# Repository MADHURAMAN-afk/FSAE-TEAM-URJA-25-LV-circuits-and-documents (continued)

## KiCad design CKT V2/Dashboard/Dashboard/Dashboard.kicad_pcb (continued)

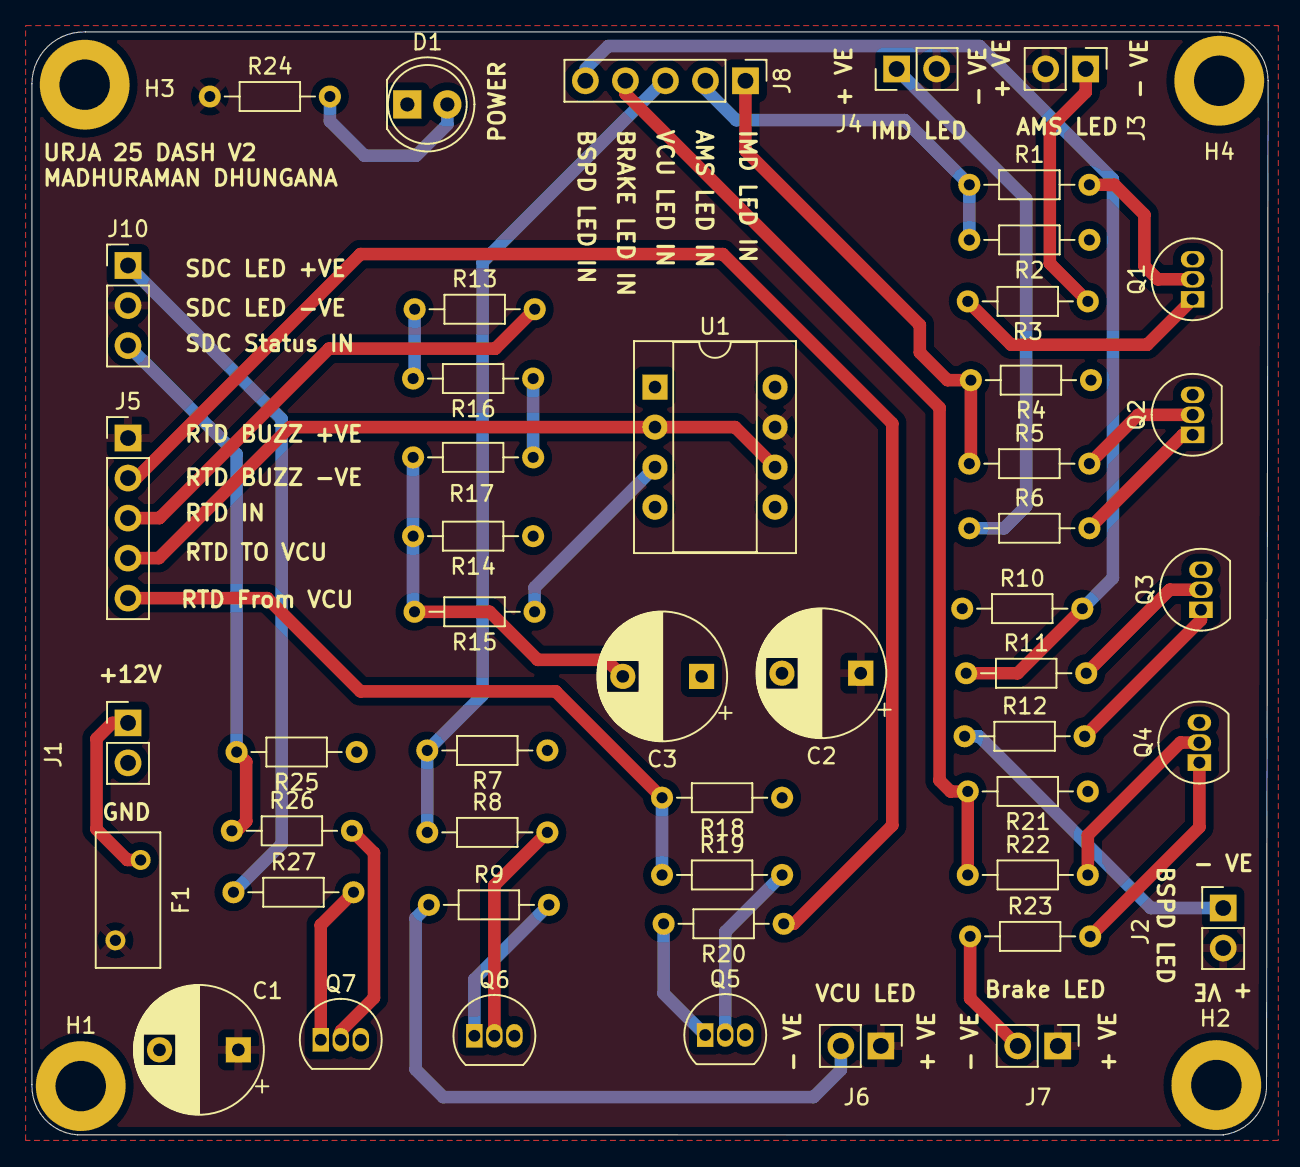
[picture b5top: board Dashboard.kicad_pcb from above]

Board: 2 copper layers, 78.5 x 70.0 mm, 53 parts (0 on the bottom side), 38 nets.

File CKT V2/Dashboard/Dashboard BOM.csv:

"Reference","Value","Qty"
"C1,C2,C3","0.1","3"
"D1","LED","1"
"F1","Polyfuse","1"
"J1,J2,J3,J4,J6,J7","Conn_01x02_Pin","6"
"J5,J8","Conn_01x05_Pin","2"
"J10","Conn_01x03_Pin","1"
"Q1,Q2,Q3,Q4,Q5,Q6,Q7","BC547","7"
"R1,R5,R8,R11,R19,R22,R26","100","7"
"R2,R4,R7,R10,R15,R18,R21,R25","10k","8"
"R3,R6,R9,R12,R20,R23,R27","220","7"
"R13","390","1"
"R14","1k","1"
"R16","2.2k","1"
"R17","10","1"
"R24","1K","1"
"U1","LM741","1"

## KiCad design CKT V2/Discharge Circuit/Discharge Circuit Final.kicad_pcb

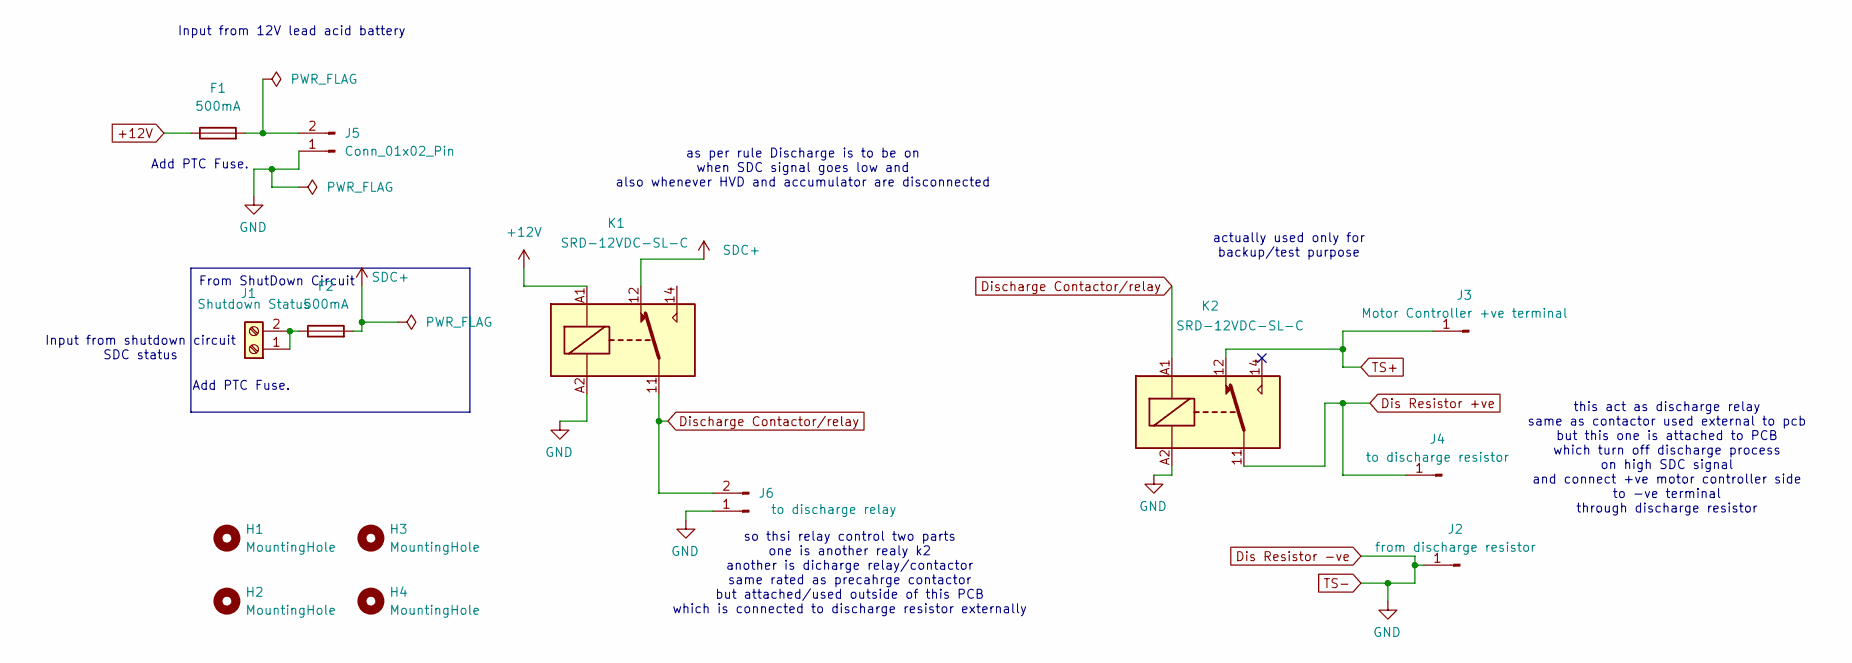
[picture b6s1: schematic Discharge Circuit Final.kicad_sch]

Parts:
F1, F2: 500mA; Fuse_BelFuse_0ZRE0008FF_L8.3mm_W3.8mm
H1, H2, H3, H4: MountingHole; MountingHole_4.3mm_M4
J1: Shutdown Status; TerminalBlock_Phoenix_MKDS-1,5-2-5.08_1x02_P5.08mm_Horizont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
J2: from discharge resistor; TerminalBlock_Phoenix_MKDS-1,5-2-5.08_1x02_P5.08mm_Horizont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
J3: Motor Controller +ve terminal; TerminalBlock_Phoenix_MKDS-1,5-2-5.08_1x02_P5.08mm_Horizont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
J4: to discharge resistor; TerminalBlock_Phoenix_MKDS-1,5-2-5.08_1x02_P5.08mm_Horizont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
J5: Conn_01x02_Pin; TerminalBlock_Phoenix_MKDS-1,5-2-5.08_1x02_P5.08mm_Horizont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
J6: to discharge relay; TerminalBlock_Phoenix_MKDS-1,5-2-5.08_1x02_P5.08mm_Horizont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
K1, K2: SRD-12VDC-SL-C; Relay_SPDT_Hongfa_HF3F-L-xx-1ZL1T

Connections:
+12V: F1.1, K1.A1
Dis Resistor +ve: J4.1, K2.11
Dis Resistor -ve: J2.1, J5.1, J6.1, K1.A2, K2.A2
Discharge Contactor/relay: J6.2, K1.11, K2.A1
unnamed: F2.1, J1.1, J1.2
unnamed: F1.2, J5.2
SDC+: F2.2, K1.12
TS+: J3.1, K2.12

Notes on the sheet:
From ShutDown Circuit
Add PTC Fuse.
as per rule Discharge is to be on when SDC signal goes low and also whenever HVD and accumulator are disconnected
actually used only for backup/test purpose
so thsi relay control two parts one is another realy k2 another is dicharge relay/contactor same rated as precahrge contactor but attached/used outside of this PCB which is connected to discharge resistor externally
Input from 12V lead acid battery
Input from shutdown circuit SDC status
this act as discharge relay same as contactor used external to pcb but this one is attached to PCB which turn off discharge process on high SDC signal and connect +ve motor controller side to -ve terminal through discharge resistor

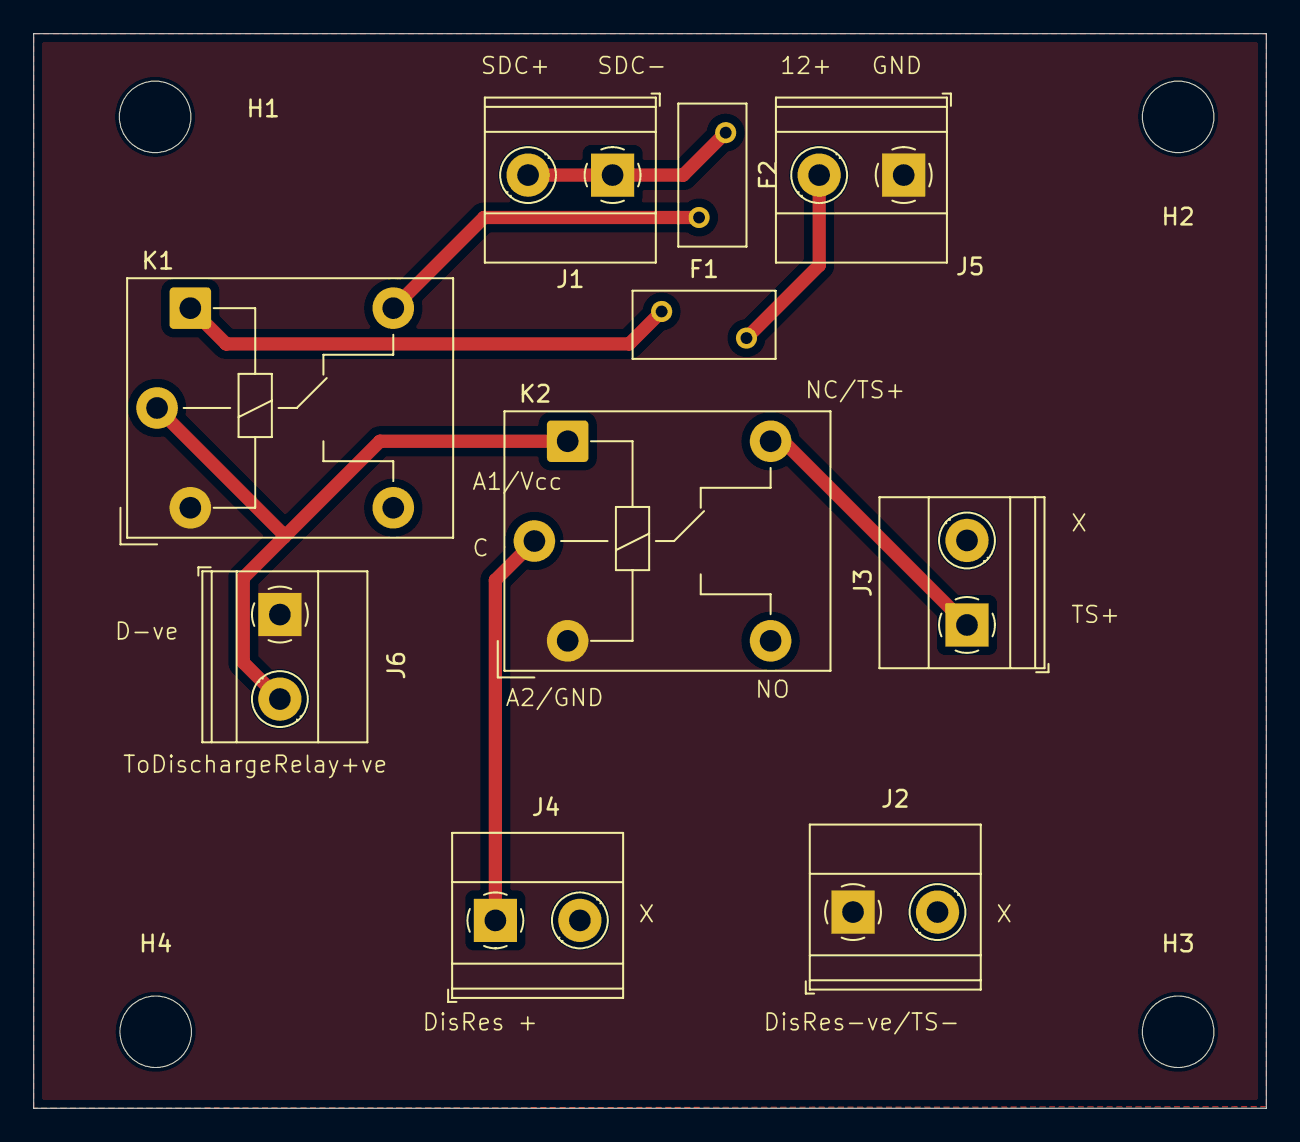
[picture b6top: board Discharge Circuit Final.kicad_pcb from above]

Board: 2 copper layers, 74.1 x 64.6 mm, 14 parts (0 on the bottom side), 8 nets.

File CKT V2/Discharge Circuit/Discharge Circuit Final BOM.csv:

Reference,Value,Footprint,Qty,DNP
"F1,F2",500mA,Fuse:Fuse_BelFuse_0ZRE0008FF_L8.3mm_W3.8mm,2,
J1,Shutdown Status,"TerminalBlock_Phoenix:TerminalBlock_Phoenix_MKDS-1,5-2-5.08_1x02_P5.08mm_Horizontal",1,
J2,from discharge resistor,"TerminalBlock_Phoenix:TerminalBlock_Phoenix_MKDS-1,5-2-5.08_1x02_P5.08mm_Horizontal",1,
J3,Motor Controller +ve terminal,"TerminalBlock_Phoenix:TerminalBlock_Phoenix_MKDS-1,5-2-5.08_1x02_P5.08mm_Horizontal",1,
J4,to discharge resistor,"TerminalBlock_Phoenix:TerminalBlock_Phoenix_MKDS-1,5-2-5.08_1x02_P5.08mm_Horizontal",1,
J5,Conn_01x02_Pin,"TerminalBlock_Phoenix:TerminalBlock_Phoenix_MKDS-1,5-2-5.08_1x02_P5.08mm_Horizontal",1,
J6,to discharge relay,"TerminalBlock_Phoenix:TerminalBlock_Phoenix_MKDS-1,5-2-5.08_1x02_P5.08mm_Horizontal",1,
"K1,K2",SRD-12VDC-SL-C,Relay_THT:Relay_SPDT_Hongfa_HF3F-L-xx-1ZL1T,2,

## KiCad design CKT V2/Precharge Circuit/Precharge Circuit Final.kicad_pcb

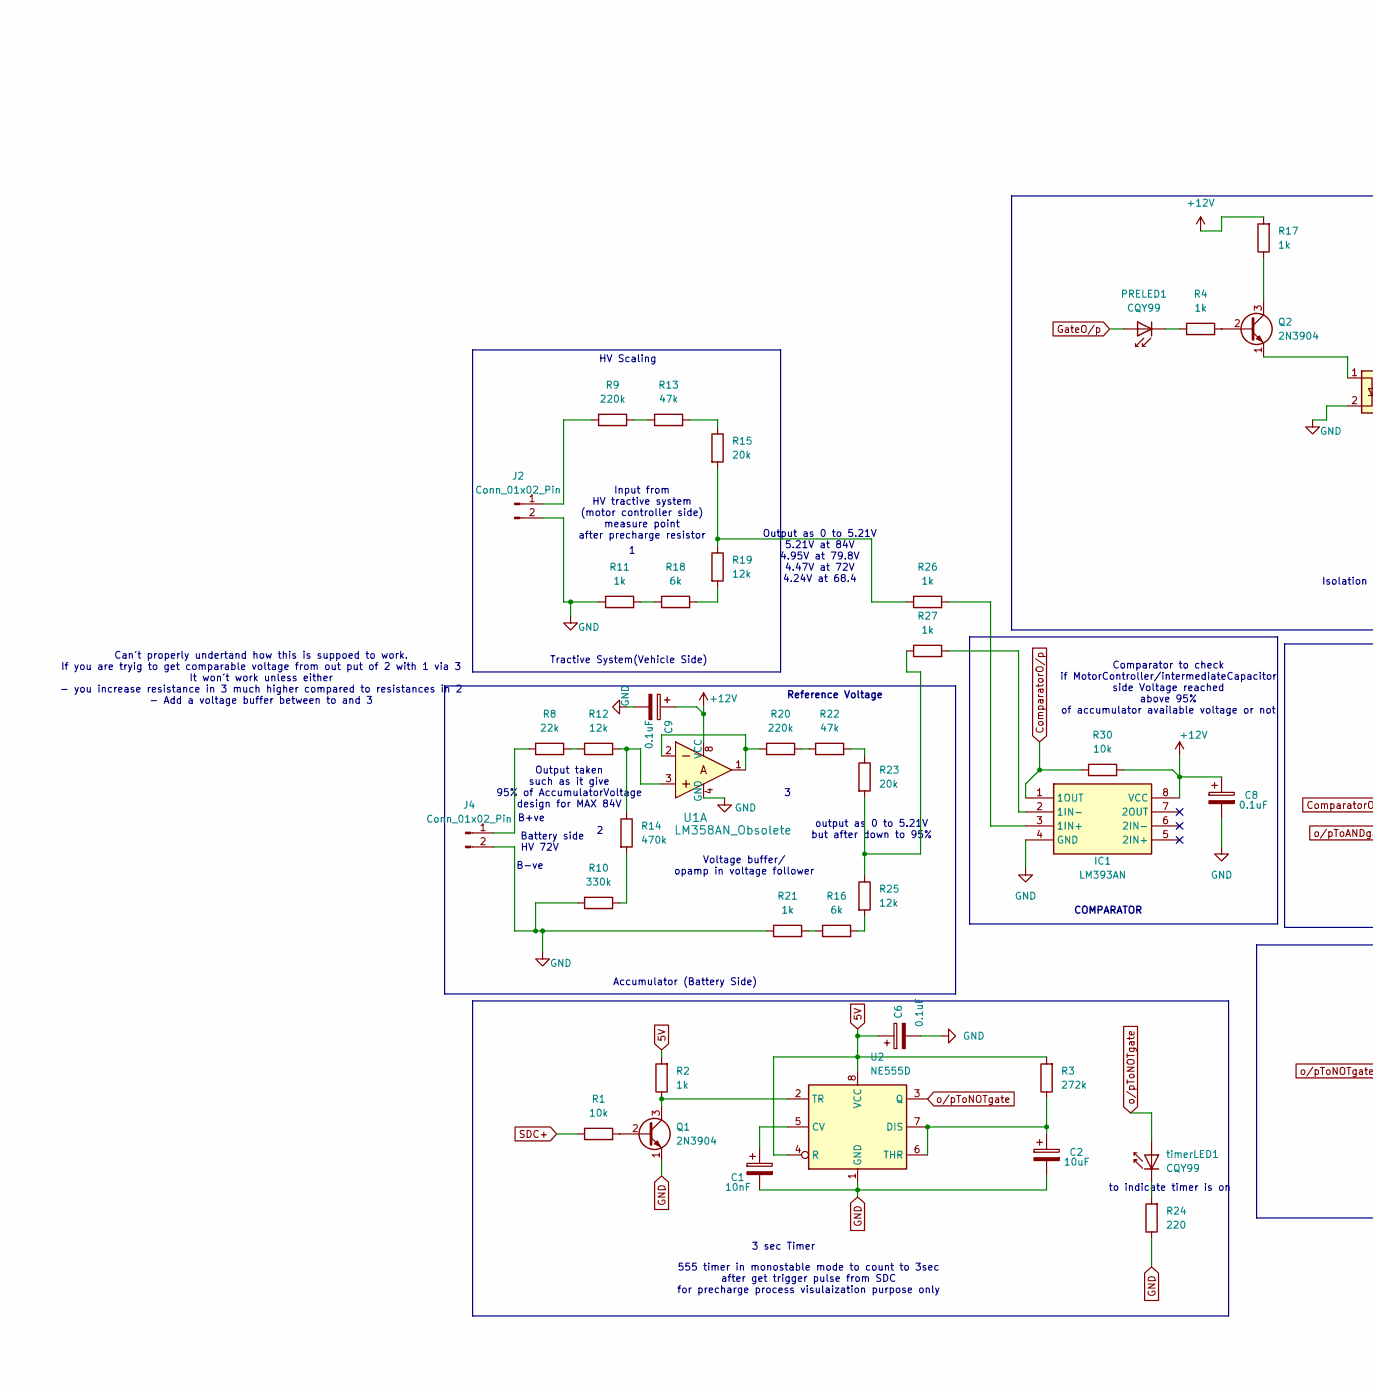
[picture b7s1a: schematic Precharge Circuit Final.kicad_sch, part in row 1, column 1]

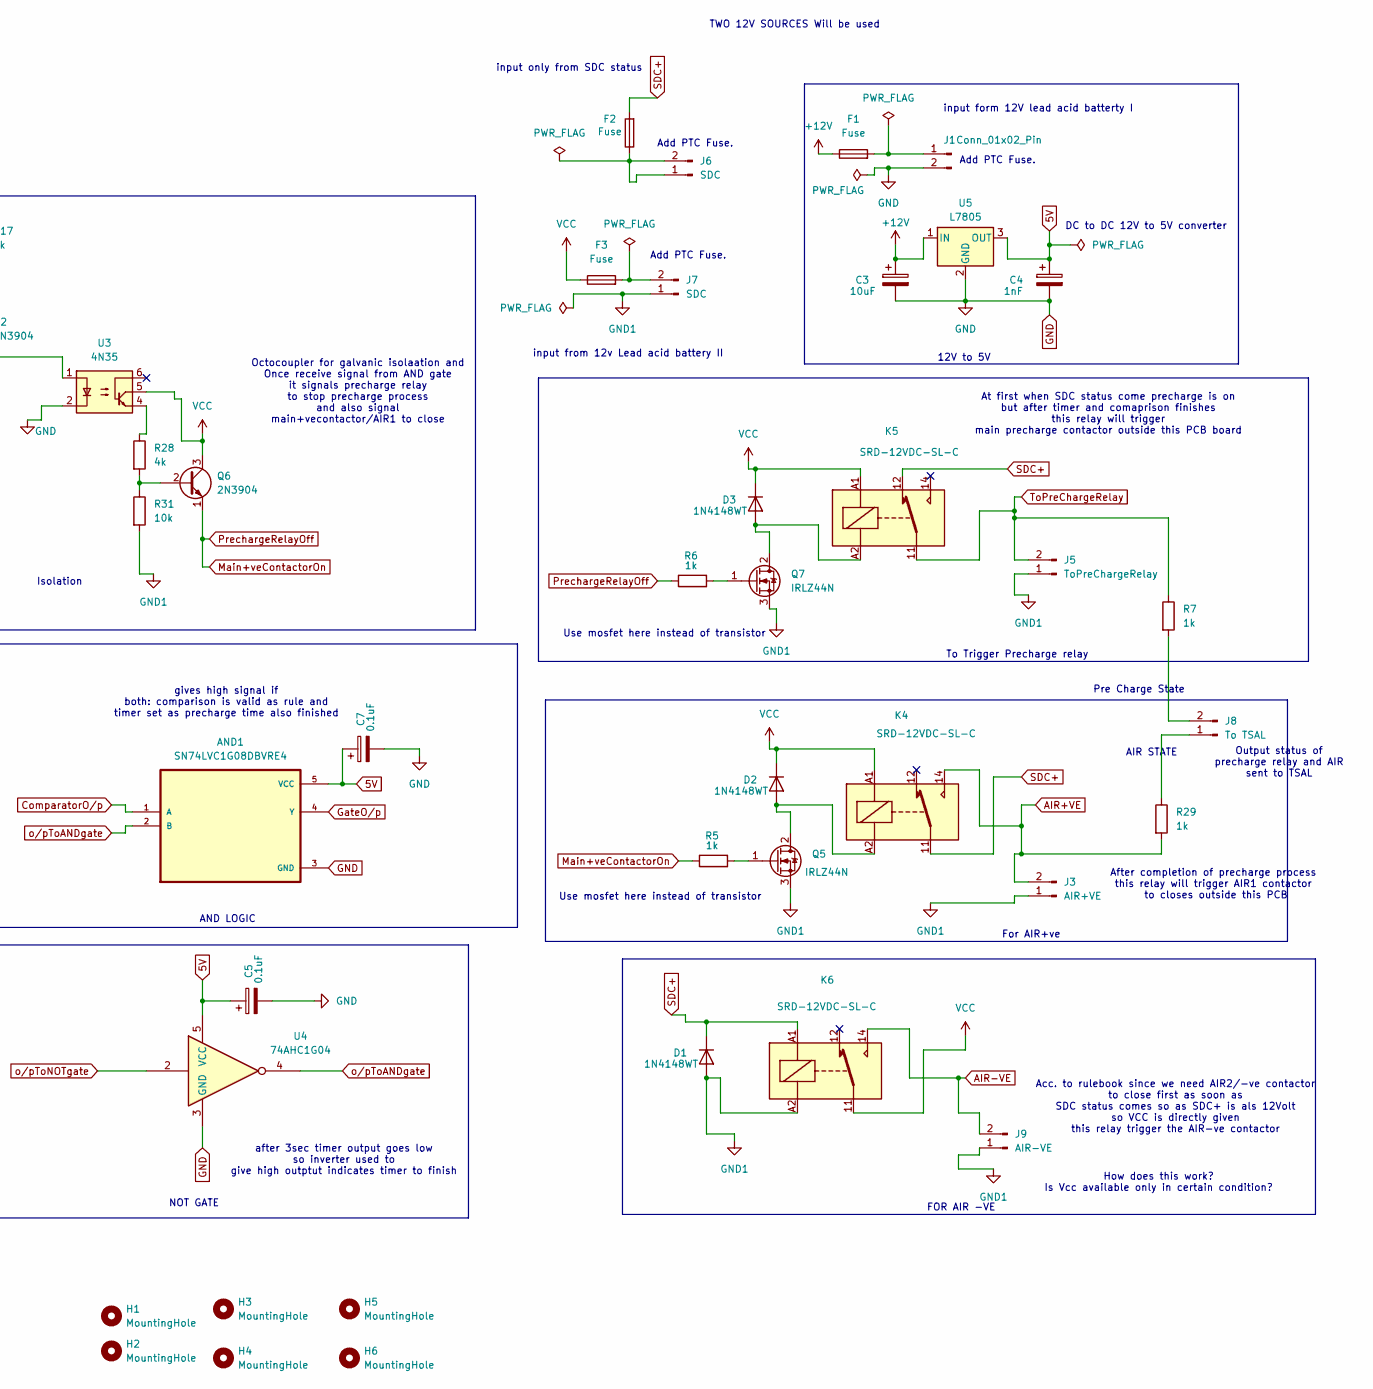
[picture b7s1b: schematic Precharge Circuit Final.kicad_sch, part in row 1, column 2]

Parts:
AND1: SN74LVC1G08DBVRE4; SOT95P280X145-5N
C1: 10nF; CP_Radial_D4.0mm_P2.00mm
C2, C3: 10uF; CP_Radial_D4.0mm_P2.00mm
C4: 1nF; CP_Radial_D4.0mm_P2.00mm
C5, C6, C7, C8, C9: 0.1uF; CP_Radial_D4.0mm_P2.00mm
D1, D2, D3: 1N4148WT; D_A-405_P7.62mm_Horizontal
F1, F2, F3: Fuse; Fuse_BelFuse_0ZRE0005FF_L8.3mm_W3.8mm
H1, H2, H3, H4, H5, H6: MountingHole; MountingHole_4.3mm_M4
IC1: LM393AN; DIP-8_W7.62mm_Socket; Manufacturer_Part_Number LM393AN; Mouser Part Number N/A
J1, J2, J4: Conn_01x02_Pin; TerminalBlock_Phoenix_MKDS-1,5-2-5.08_1x02_P5.08mm_Horizont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
J3: AIR+VE; TerminalBlock_Phoenix_MKDS-1,5-2-5.08_1x02_P5.08mm_Horizont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
J5: ToPreChargeRelay; TerminalBlock_Phoenix_MKDS-1,5-2-5.08_1x02_P5.08mm_Horizont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
J6, J7: SDC; TerminalBlock_Phoenix_MKDS-1,5-2-5.08_1x02_P5.08mm_Horizont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
J8: To TSAL; TerminalBlock_Phoenix_MKDS-1,5-2-5.08_1x02_P5.08mm_Horizont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
J9: AIR-VE; TerminalBlock_Phoenix_MKDS-1,5-2-5.08_1x02_P5.08mm_Horizont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
K4, K5, K6: SRD-12VDC-SL-C; Relay_SPDT_Hongfa_HF3F-L-xx-1ZL1T
PRELED1: CQY99; LED_D5.0mm_IRGrey
Q1, Q2, Q6: 2N3904; TO-92_Inline_Wide
Q5, Q7: IRLZ44N; TO-220-3_Vertical
R1, R30, R31: 10k; R_Axial_DIN0207_L6.3mm_D2.5mm_P10.16mm_Horizontal
R2, R4, R5, R6, R7, R11, R17, R21, R26, R27, R29: 1k; R_Axial_DIN0207_L6.3mm_D2.5mm_P10.16mm_Horizontal
R3: 272k; R_Axial_DIN0207_L6.3mm_D2.5mm_P10.16mm_Horizontal
R8: 22k; R_Axial_DIN0207_L6.3mm_D2.5mm_P10.16mm_Horizontal
R9, R20: 220k; R_Axial_DIN0207_L6.3mm_D2.5mm_P10.16mm_Horizontal
R10: 330k; R_Axial_DIN0207_L6.3mm_D2.5mm_P10.16mm_Horizontal
R12, R19, R25: 12k; R_Axial_DIN0207_L6.3mm_D2.5mm_P10.16mm_Horizontal
R13, R22: 47k; R_Axial_DIN0207_L6.3mm_D2.5mm_P10.16mm_Horizontal
R14: 470k; R_Axial_DIN0207_L6.3mm_D2.5mm_P10.16mm_Horizontal
R15, R23: 20k; R_Axial_DIN0207_L6.3mm_D2.5mm_P10.16mm_Horizontal
R16, R18: 6k; R_Axial_DIN0207_L6.3mm_D2.5mm_P10.16mm_Horizontal
R24: 220; R_Axial_DIN0207_L6.3mm_D2.5mm_P10.16mm_Horizontal
R28: 4k; R_Axial_DIN0207_L6.3mm_D2.5mm_P10.16mm_Horizontal
U1: LM358AN_Obsolete; DIP-8_W7.62mm; MPN LM358AN; Digi-Key_PN LM358ANFS-ND
U2: NE555D; DIP-8_W7.62mm
U3: 4N35; DIP-6_W7.62mm
U4: 74AHC1G04; SOT-23-5
U5: L7805; TO-220-3_Vertical
timerLED1: CQY99; LED_D5.0mm_IRGrey

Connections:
5V: AND1.5 (VCC), C4.1, C5.1, C6.1, C7.1, R2.2, R3.2, U2.4 (R), U2.8 (VCC), U4.5 (VCC), U5.3 (OUT)
+12V: C3.1, C8.1, C9.1, F1.1, IC1.8 (VCC), R17.2, R30.2, U1.8 (VCC), U5.1 (IN)
AIR+VE: J3.2, K4.14, R29.2
AIR-VE: J9.2, K6.14
ComparatorO/p: AND1.1 (A), IC1.1 (1OUT), R30.1
GND: AND1.3 (GND), C1.2, C2.2, C3.2, C4.2, C5.2, C6.2, C7.2, C8.2, C9.2, IC1.4 (GND), J1.2, J2.2, J4.2, Q1.1 (E), R10.2, R11.1, R21.1, R24.1, U1.4 (GND), U2.1 (GND), U3.2, U4.3 (GND), U5.2 (GND)
GND1: D1.2 (A), J3.1, J5.1, J7.1, J9.1, K6.A2, Q5.3 (S), Q7.3 (S), R31.2
GateO/p: AND1.4 (Y), PRELED1.2 (A)
Main+veContactorOn: Q6.1 (E), R5.1, R6.1
unnamed: D2.2 (A), K4.A2, Q5.2 (D)
unnamed: D3.2 (A), K5.A2, Q7.2 (D)
unnamed: IC1.3 (1IN+), R26.2
unnamed: IC1.2 (1IN-), R27.2
unnamed: F1.2, J1.1
unnamed: J2.1, R9.2
unnamed: J4.1, R8.2
unnamed: F2.1, J6.1, J6.2
unnamed: F3.2, J7.2
unnamed: J8.1, R29.1
unnamed: J8.2, R7.2
unnamed: PRELED1.1 (K), R4.1
unnamed: Q1.2 (B), R1.2
unnamed: Q1.3 (C), R2.1, U2.2 (TR)
unnamed: Q2.2 (B), R4.2
unnamed: Q2.3 (C), R17.1
unnamed: Q2.1 (E), U3.1
unnamed: Q5.1 (G), R5.2
unnamed: Q6.2 (B), R28.2, R31.1
unnamed: Q7.1 (G), R6.2
unnamed: R10.1, R14.2
unnamed: R11.2, R18.1
unnamed: R8.1, R12.1
unnamed: R12.2, R14.1, U1.3
unnamed: R9.1, R13.1
unnamed: R13.2, R15.1
unnamed: R15.2, R19.1, R26.1
unnamed: R16.1, R21.2
unnamed: R16.2, R25.2
unnamed: R18.2, R19.2
unnamed: R20.1, R22.1
unnamed: R20.2, U1.1, U1.2
unnamed: R22.2, R23.1
unnamed: R23.2, R25.1, R27.1
unnamed: R28.1, U3.4
unnamed: C1.1, U2.5 (CV)
unnamed: C2.1, R3.1, U2.6 (THR), U2.7 (DIS)
unnamed: R24.2, timerLED1.1 (K)
SDC+: D1.1 (K), F2.2, K4.11, K5.12, K6.A1, R1.1
ToPreChargeRelay: J5.2, K5.11, R7.1
VCC: D2.1 (K), D3.1 (K), F3.1, K4.A1, K5.A1, K6.11, Q6.3 (C), U3.5
o/pToANDgate: AND1.2 (B), U4.4
o/pToNOTgate: U2.3 (Q), U4.2, timerLED1.2 (A)

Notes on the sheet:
Acc. to rulebook since we need AIR2/-ve contactor to close first as soon as SDC status comes so as SDC+ is als 12Volt so VCC is directly given this relay trigger the AIR-ve contactor
B+ve
FOR AIR -VE
After completion of precharge process this relay will trigger AIR1 contactor to closes outside this PCB
TWO 12V SOURCES Will be used
Output taken such as it give 95% of AccumulatorVoltage design for MAX 84V
B-ve
Battery side
output as 0 to 5.21V but after down to 95%
Add PTC Fuse.
COMPARATOR
Output status of precharge relay and AIR sent to TSAL
input only from SDC status
NOT GATE
Comparator to check if MotorController/intermediateCapacitor side Voltage reached above 95% of accumulator available voltage or not
Isolation
How does this work? Is Vcc available only in certain condition?
At first when SDC status come precharge is on but after timer and comaprison finishes this relay will trigger main precharge contactor outside this PCB board
Use mosfet here instead of transistor
3 sec Timer
after 3sec timer output goes low so inverter used to give high outptut indicates timer to finish
Reference Voltage
Pre Charge State
12V to 5V
555 timer in monostable mode to count to 3sec after get trigger pulse from SDC for precharge process visulaization purpose only
gives high signal if both: comparison is valid as rule and timer set as precharge time also finished
input form 12V lead acid batterty I
Output as 0 to 5.21V 5.21V at 84V 4.95V at 79.8V 4.47V at 72V 4.24V at 68.4
AIR STATE
DC to DC 12V to 5V converter
Tractive System(Vehicle Side)
HV 72V
Octocoupler for galvanic isolaation and Once receive signal from AND gate it signals precharge relay to stop precharge process and also signal main+vecontactor/AIR1 to close
Voltage buffer/ opamp in voltage follower
HV Scaling
Input from HV tractive system (motor controller side) measure point after precharge resistor
For AIR+ve
AND LOGIC
to indicate timer is on
Accumulator (Battery Side)

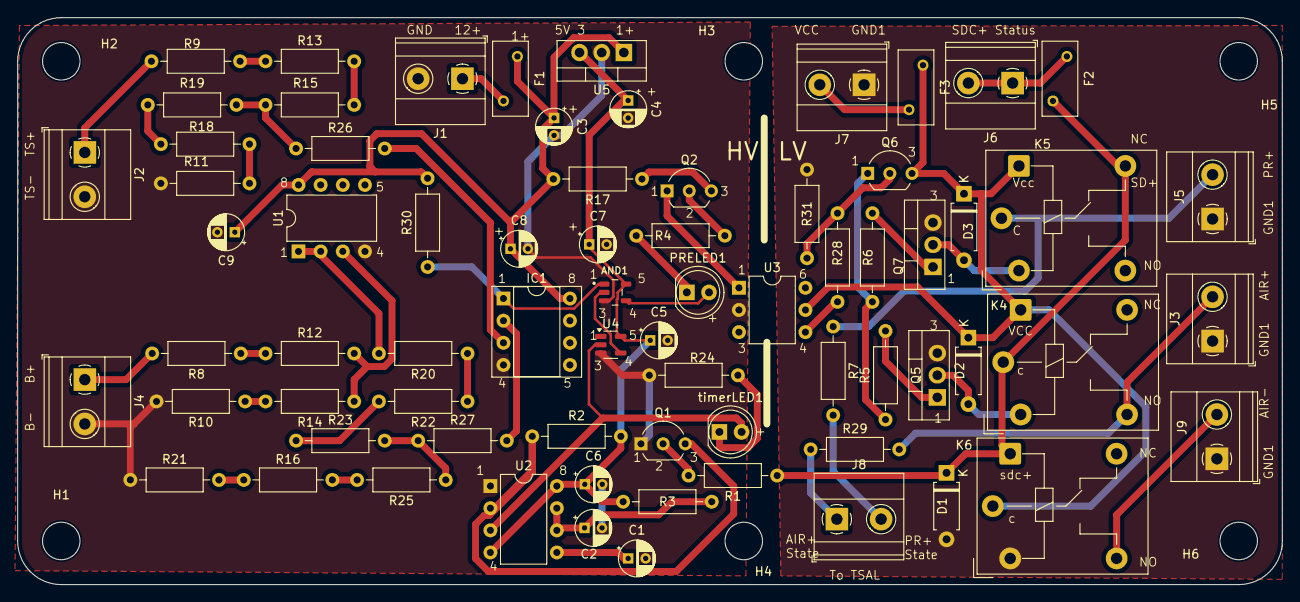
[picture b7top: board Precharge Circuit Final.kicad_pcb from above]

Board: 2 copper layers, 145.0 x 65.0 mm, 78 parts (0 on the bottom side), 52 nets.

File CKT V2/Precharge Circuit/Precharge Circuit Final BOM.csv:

Reference,Value,Footprint,Qty,DNP
AND1,SN74LVC1G08DBVRE4,SN74LVC1G08DBVRE4:SOT95P280X145-5N,1,
C1,10nF,Capacitor_THT:CP_Radial_D4.0mm_P2.00mm,1,
"C2,C3",10uF,Capacitor_THT:CP_Radial_D4.0mm_P2.00mm,2,
C4,1nF,Capacitor_THT:CP_Radial_D4.0mm_P2.00mm,1,
"C5,C6,C7,C8,C9",0.1uF,Capacitor_THT:CP_Radial_D4.0mm_P2.00mm,5,
"D1,D2,D3",1N4148WT,Diode_THT:D_A-405_P7.62mm_Horizontal,3,
"F1,F2,F3",Fuse,Fuse:Fuse_BelFuse_0ZRE0005FF_L8.3mm_W3.8mm,3,
IC1,LM393AN,Package_DIP:DIP-8_W7.62mm_Socket,1,
"J1,J2,J4",Conn_01x02_Pin,"TerminalBlock_Phoenix:TerminalBlock_Phoenix_MKDS-1,5-2-5.08_1x02_P5.08mm_Horizontal",3,
J3,AIR+VE,"TerminalBlock_Phoenix:TerminalBlock_Phoenix_MKDS-1,5-2-5.08_1x02_P5.08mm_Horizontal",1,
J5,ToPreChargeRelay,"TerminalBlock_Phoenix:TerminalBlock_Phoenix_MKDS-1,5-2-5.08_1x02_P5.08mm_Horizontal",1,
"J6,J7",SDC,"TerminalBlock_Phoenix:TerminalBlock_Phoenix_MKDS-1,5-2-5.08_1x02_P5.08mm_Horizontal",2,
J8,To TSAL,"TerminalBlock_Phoenix:TerminalBlock_Phoenix_MKDS-1,5-2-5.08_1x02_P5.08mm_Horizontal",1,
J9,AIR-VE,"TerminalBlock_Phoenix:TerminalBlock_Phoenix_MKDS-1,5-2-5.08_1x02_P5.08mm_Horizontal",1,
"K4,K5,K6",SRD-12VDC-SL-C,Relay_THT:Relay_SPDT_Hongfa_HF3F-L-xx-1ZL1T,3,
"PRELED1,timerLED1",CQY99,LED_THT:LED_D5.0mm_IRGrey,2,
"Q1,Q2,Q6",2N3904,Package_TO_SOT_THT:TO-92_Inline_Wide,3,
"Q5,Q7",IRLZ44N,Package_TO_SOT_THT:TO-220-3_Vertical,2,
"R1,R30,R31",10k,Resistor_THT:R_Axial_DIN0207_L6.3mm_D2.5mm_P10.16mm_Horizontal,3,
"R2,R4,R5,R6,R7,R11,R17,R21,R26,R27,R29",1k,Resistor_THT:R_Axial_DIN0207_L6.3mm_D2.5mm_P10.16mm_Horizontal,11,
R3,272k,Resistor_THT:R_Axial_DIN0207_L6.3mm_D2.5mm_P10.16mm_Horizontal,1,
R8,22k,Resistor_THT:R_Axial_DIN0207_L6.3mm_D2.5mm_P10.16mm_Horizontal,1,
"R9,R20",220k,Resistor_THT:R_Axial_DIN0207_L6.3mm_D2.5mm_P10.16mm_Horizontal,2,
R10,330k,Resistor_THT:R_Axial_DIN0207_L6.3mm_D2.5mm_P10.16mm_Horizontal,1,
"R12,R19,R25",12k,Resistor_THT:R_Axial_DIN0207_L6.3mm_D2.5mm_P10.16mm_Horizontal,3,
"R13,R22",47k,Resistor_THT:R_Axial_DIN0207_L6.3mm_D2.5mm_P10.16mm_Horizontal,2,
R14,470k,Resistor_THT:R_Axial_DIN0207_L6.3mm_D2.5mm_P10.16mm_Horizontal,1,
"R15,R23",20k,Resistor_THT:R_Axial_DIN0207_L6.3mm_D2.5mm_P10.16mm_Horizontal,2,
"R16,R18",6k,Resistor_THT:R_Axial_DIN0207_L6.3mm_D2.5mm_P10.16mm_Horizontal,2,
R24,220,Resistor_THT:R_Axial_DIN0207_L6.3mm_D2.5mm_P10.16mm_Horizontal,1,
R28,4k,Resistor_THT:R_Axial_DIN0207_L6.3mm_D2.5mm_P10.16mm_Horizontal,1,
U1,LM358AN_Obsolete,Package_DIP:DIP-8_W7.62mm,1,
U2,NE555D,Package_DIP:DIP-8_W7.62mm,1,
U3,4N35,Package_DIP:DIP-6_W7.62mm,1,
U4,74AHC1G04,Package_TO_SOT_SMD:SOT-23-5,1,
U5,L7805,Package_TO_SOT_THT:TO-220-3_Vertical,1,

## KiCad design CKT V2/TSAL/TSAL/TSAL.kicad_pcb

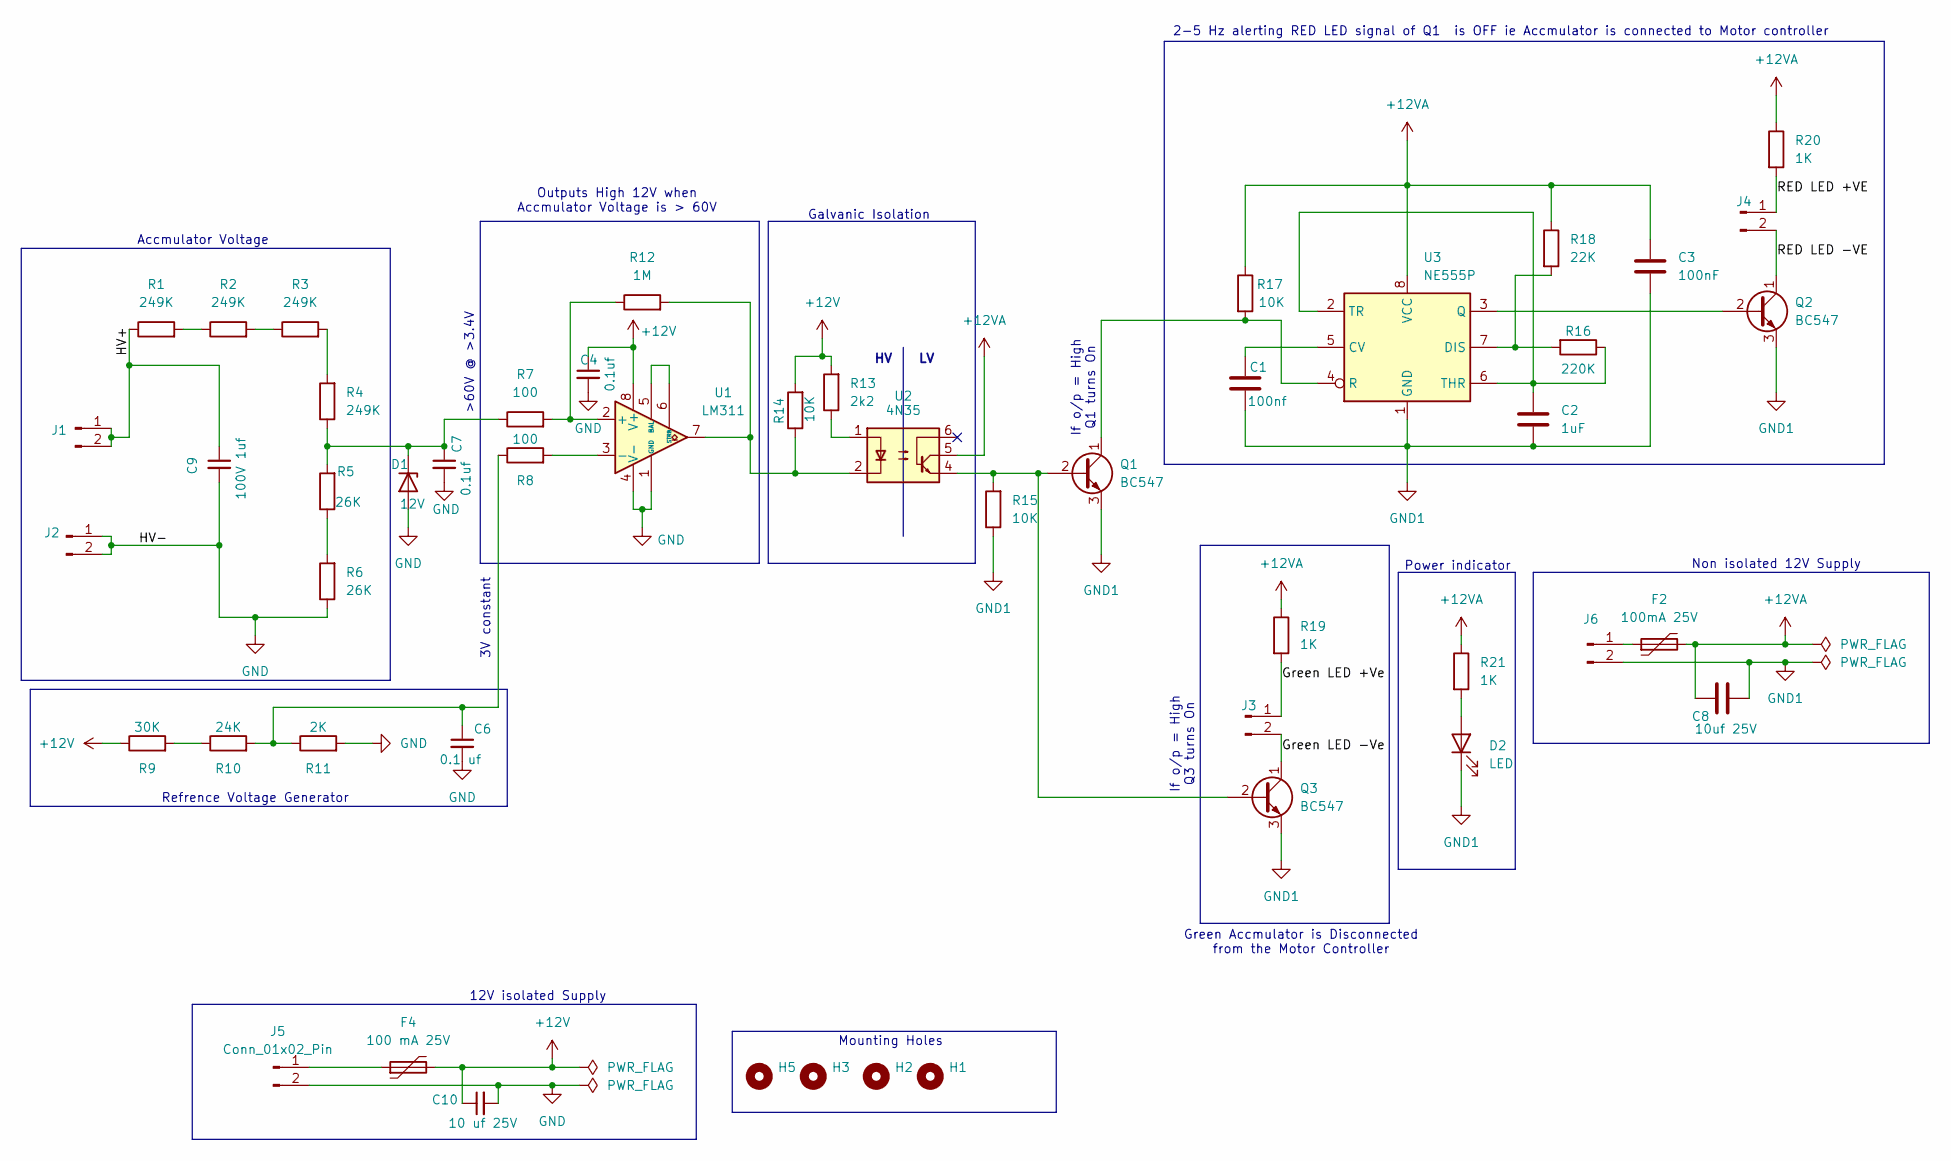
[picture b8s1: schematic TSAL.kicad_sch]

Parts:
C1: 100nf; CP_Radial_D10.0mm_P5.00mm
C2: 1uF; CP_Radial_D10.0mm_P5.00mm
C3: 100nF; CP_Radial_D10.0mm_P5.00mm
C4, C7: 0.1uf; CP_Radial_D10.0mm_P5.00mm
C6: 0.1 uf; CP_Radial_D10.0mm_P5.00mm
C8: 10uf 25V; CP_Radial_D10.0mm_P5.00mm
C9: 100V 1uf; CP_Radial_D10.0mm_P5.00mm
C10: 10 uf 25V; CP_Radial_D10.0mm_P5.00mm
D1: 12V; D_A-405_P7.62mm_Horizontal
D2: LED; LED_D5.0mm
F2: 100mA 25V; Fuse_BelFuse_0ZRE0012FF_L8.3mm_W3.8mm
F4: 100 mA 25V; Fuse_BelFuse_0ZRE0012FF_L8.3mm_W3.8mm
H1, H2, H3, H5: MountingHole; MountingHole_4.3mm_M4
J1: HV +; TerminalBlock_Phoenix_MKDS-1,5-2-5.08_1x02_P5.08mm_Horizont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
J2, J3, J4, J5, J6: Conn_01x02_Pin; TerminalBlock_Phoenix_MKDS-1,5-2-5.08_1x02_P5.08mm_Horizont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
Q1, Q2, Q3: BC547; TO-92_Inline
R1, R2, R3, R4: 249K; R_Axial_DIN0207_L6.3mm_D2.5mm_P7.62mm_Horizontal
R5, R6: 26K; R_Axial_DIN0207_L6.3mm_D2.5mm_P7.62mm_Horizontal
R7, R8: 100; R_Axial_DIN0207_L6.3mm_D2.5mm_P7.62mm_Horizontal
R9: 30K; R_Axial_DIN0207_L6.3mm_D2.5mm_P7.62mm_Horizontal
R10: 24K; R_Axial_DIN0207_L6.3mm_D2.5mm_P7.62mm_Horizontal
R11: 2K; R_Axial_DIN0207_L6.3mm_D2.5mm_P7.62mm_Horizontal
R12: 1M; R_Axial_DIN0207_L6.3mm_D2.5mm_P7.62mm_Horizontal
R13: 2k2; R_Axial_DIN0207_L6.3mm_D2.5mm_P7.62mm_Horizontal
R14, R15, R17: 10K; R_Axial_DIN0207_L6.3mm_D2.5mm_P7.62mm_Horizontal
R16: 220K; R_Axial_DIN0207_L6.3mm_D2.5mm_P7.62mm_Horizontal
R18: 22K; R_Axial_DIN0207_L6.3mm_D2.5mm_P7.62mm_Horizontal
R19, R20, R21: 1K; R_Axial_DIN0207_L6.3mm_D2.5mm_P7.62mm_Horizontal
U1: LM311; CERDIP-8_W7.62mm_SideBrazed
U2: 4N35; DIP-6_W7.62mm
U3: NE555P; DIP-8_W7.62mm

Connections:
+12V: C4.1, C10.1, F4.2, R9.1, R13.2, R14.2, U1.8 (V+)
+12VA: C3.1, C8.1, F2.2, R17.1, R18.1, R19.1, R20.1, R21.1, U2.5, U3.8 (VCC)
/Green LED +Ve: J3.1, R19.2
/Green LED -Ve: J3.2, Q3.1 (C)
/HV+: C9.1, J1.1, J1.2, R1.1
/RED LED +VE: J4.1, R20.2
/RED LED -VE: J4.2, Q2.1 (C)
GND: C4.2, C6.2, C7.2, C9.2, C10.2, D1.2 (A), J2.1, J2.2, J5.2, R6.1, R11.2, U1.1 (GND), U1.4 (V-)
GND1: C1.2, C2.2, C3.2, C8.2, D2.1 (K), J6.2, Q1.3 (E), Q2.3 (E), Q3.3 (E), R15.1, U3.1 (GND)
unnamed: C6.1, R8.1, R10.2, R11.1
unnamed: C7.1, D1.1 (K), R4.1, R5.2, R7.1
unnamed: D2.2 (A), R21.2
unnamed: F4.1, J5.1
unnamed: F2.1, J6.1
unnamed: Q1.2 (B), Q3.2 (B), R15.2, U2.4
unnamed: Q1.1 (C), R17.2, U3.4 (R)
unnamed: Q2.2 (B), U3.3 (Q)
unnamed: R1.2, R2.1
unnamed: R2.2, R3.1
unnamed: R3.2, R4.2
unnamed: R5.1, R6.2
unnamed: R9.2, R10.1
unnamed: R12.2, R14.1, U1.7, U2.2
unnamed: R13.1, U2.1
unnamed: R7.2, R12.1, U1.2 (+)
unnamed: R8.2, U1.3 (-)
unnamed: U1.5 (BAL), U1.6 (STRB)
unnamed: C1.1, U3.5 (CV)
unnamed: R16.2, R18.2, U3.7 (DIS)
unnamed: C2.1, R16.1, U3.2 (TR), U3.6 (THR)

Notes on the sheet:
2-5 Hz alerting RED LED signal of Q1 is OFF ie Accmulator is connected to Motor controller
>60V @ >3.4V
If o/p = High Q3 turns On
Accmulator Voltage
If o/p = High Q1 turns On
Outputs High 12V when Accmulator Voltage is > 60V
Galvanic Isolation
3V constant
Mounting Holes
Non isolated 12V Supply
Refrence Voltage Generator
Power indicator
12V isolated Supply
Green Accmulator is Disconnected from the Motor Controller

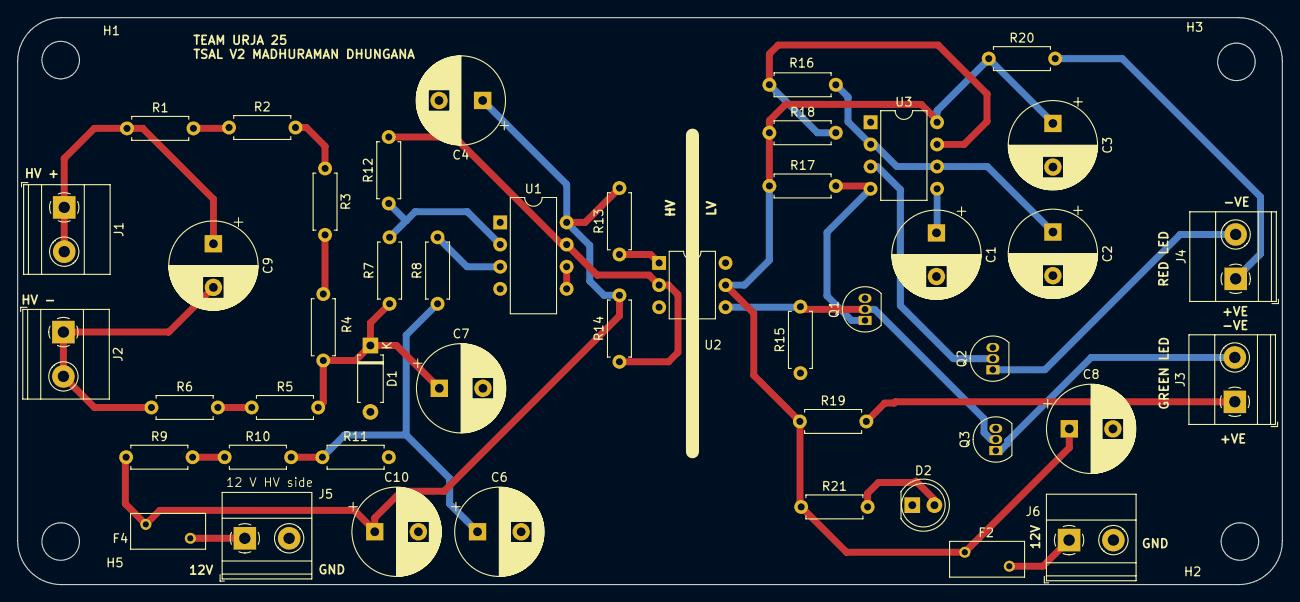
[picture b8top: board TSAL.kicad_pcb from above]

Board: 2 copper layers, 145.0 x 65.0 mm, 50 parts (0 on the bottom side), 30 nets.

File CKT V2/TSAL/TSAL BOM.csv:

Reference,Value,Qty,DNP
C1,100nf,1,
C2,1uF,1,
C3,100nF,1,
"C4,C7",0.1uf,2,
C6,0.1 uf,1,
C8,10uf 25V,1,
C9,100V 1uf,1,
C10,10 uf 25V,1,
D1,12V,1,
D2,LED,1,
F2,100mA 25V,1,
F4,100 mA 25V,1,
J1,HV +,1,
"J2,J3,J4,J5,J6",Conn_01x02_Pin,5,
"Q1,Q2,Q3",BC547,3,
"R1,R2,R3,R4",249K,4,
"R5,R6",26K,2,
"R7,R8",100,2,
R9,30K,1,
R10,24K,1,
R11,2K,1,
R12,1M,1,
R13,2k2,1,
"R14,R15,R17",10K,3,
R16,220K,1,
R18,22K,1,
"R19,R20,R21",1K,3,
U1,LM311,1,
U2,4N35,1,
U3,NE555P,1,
